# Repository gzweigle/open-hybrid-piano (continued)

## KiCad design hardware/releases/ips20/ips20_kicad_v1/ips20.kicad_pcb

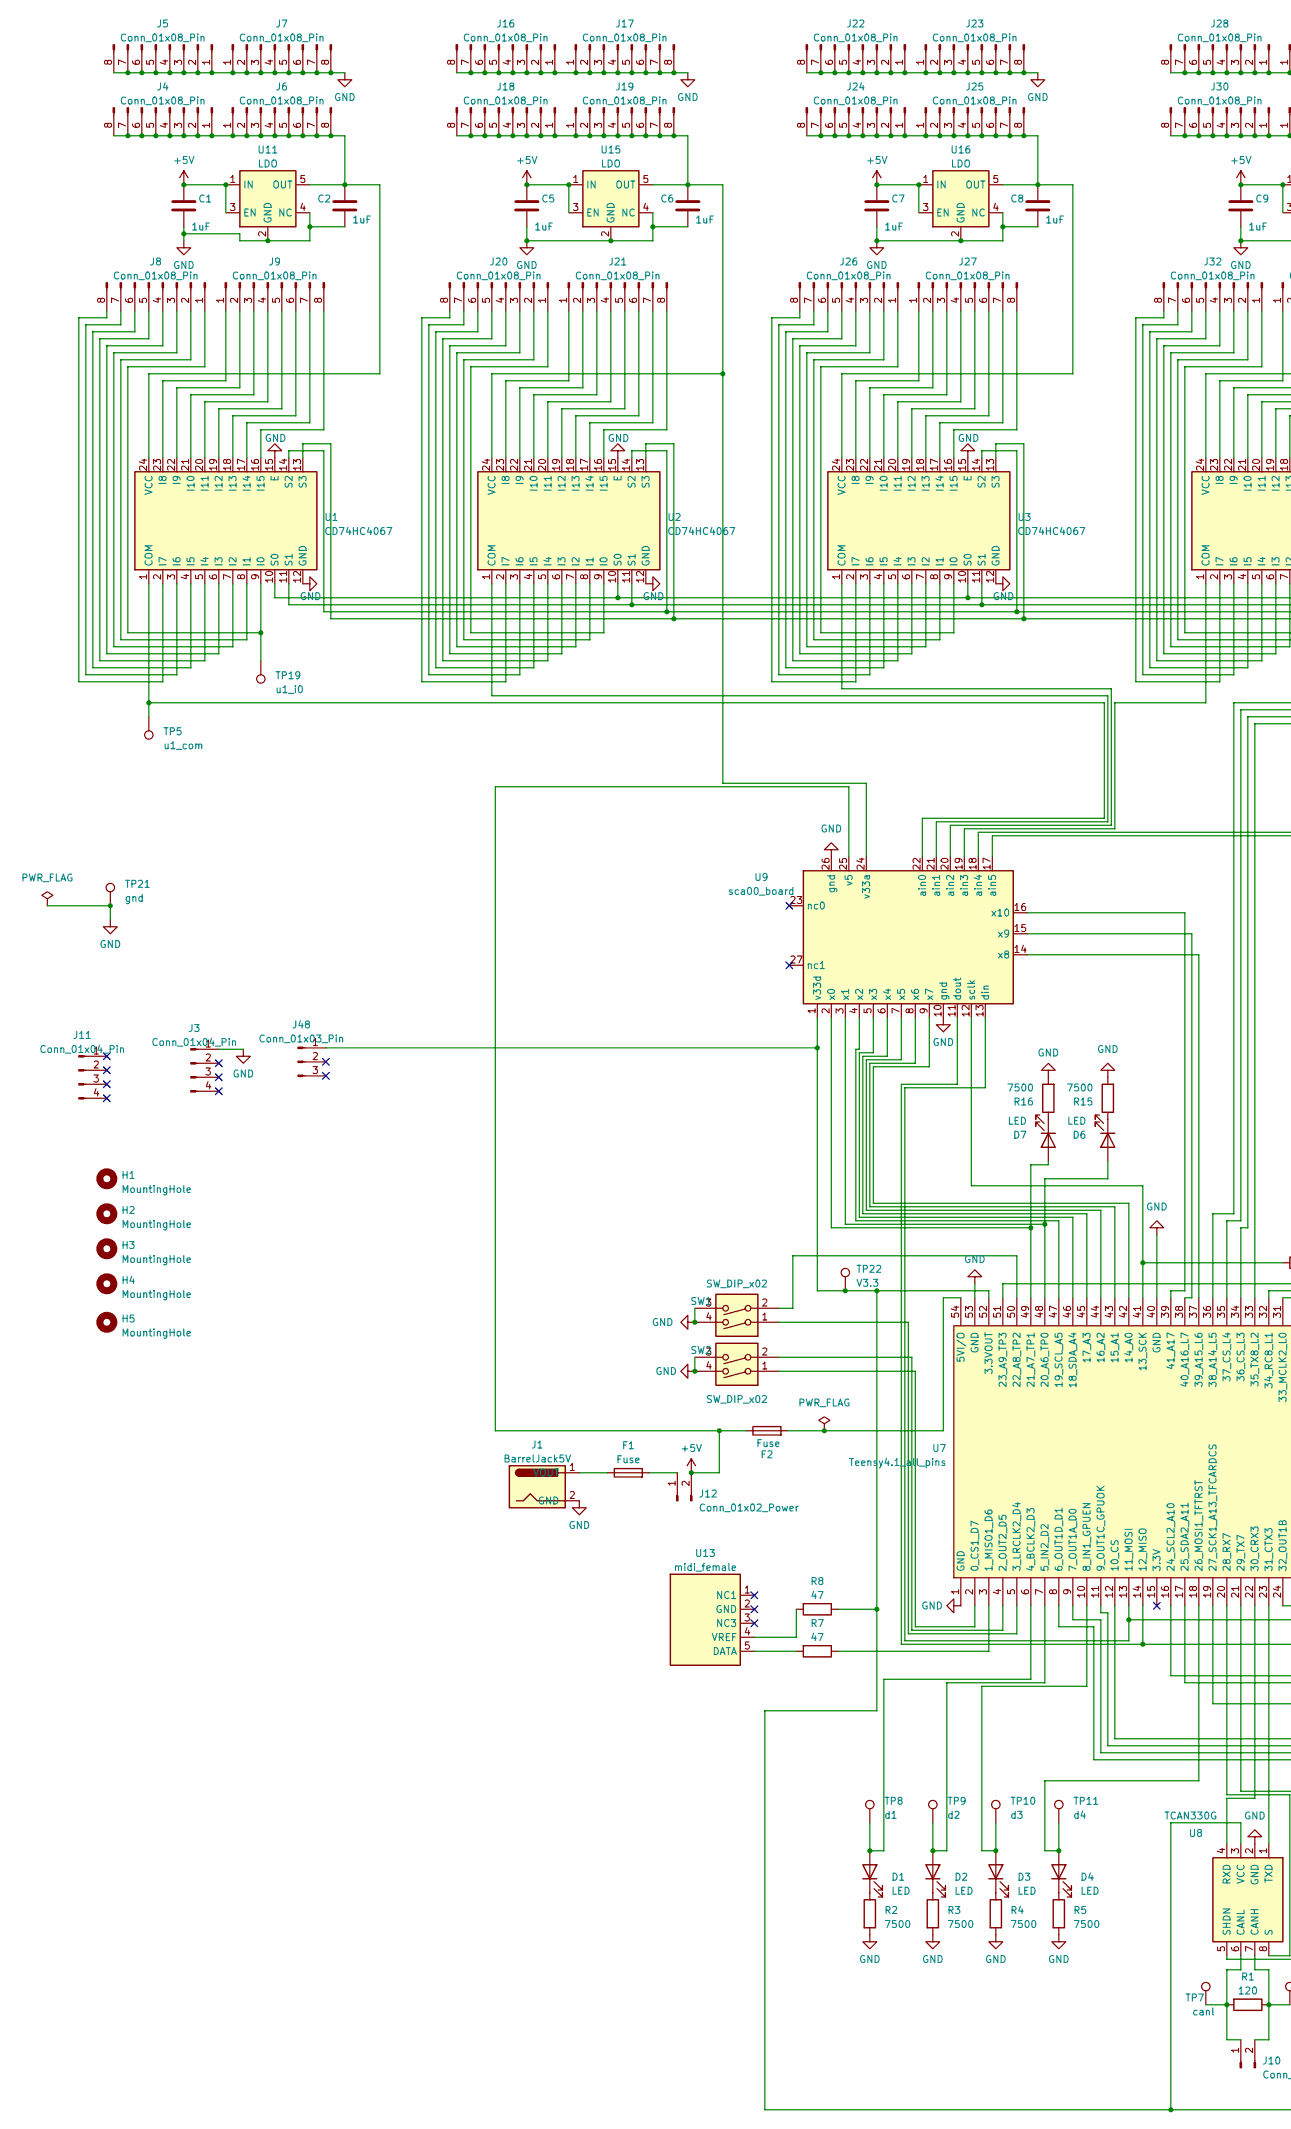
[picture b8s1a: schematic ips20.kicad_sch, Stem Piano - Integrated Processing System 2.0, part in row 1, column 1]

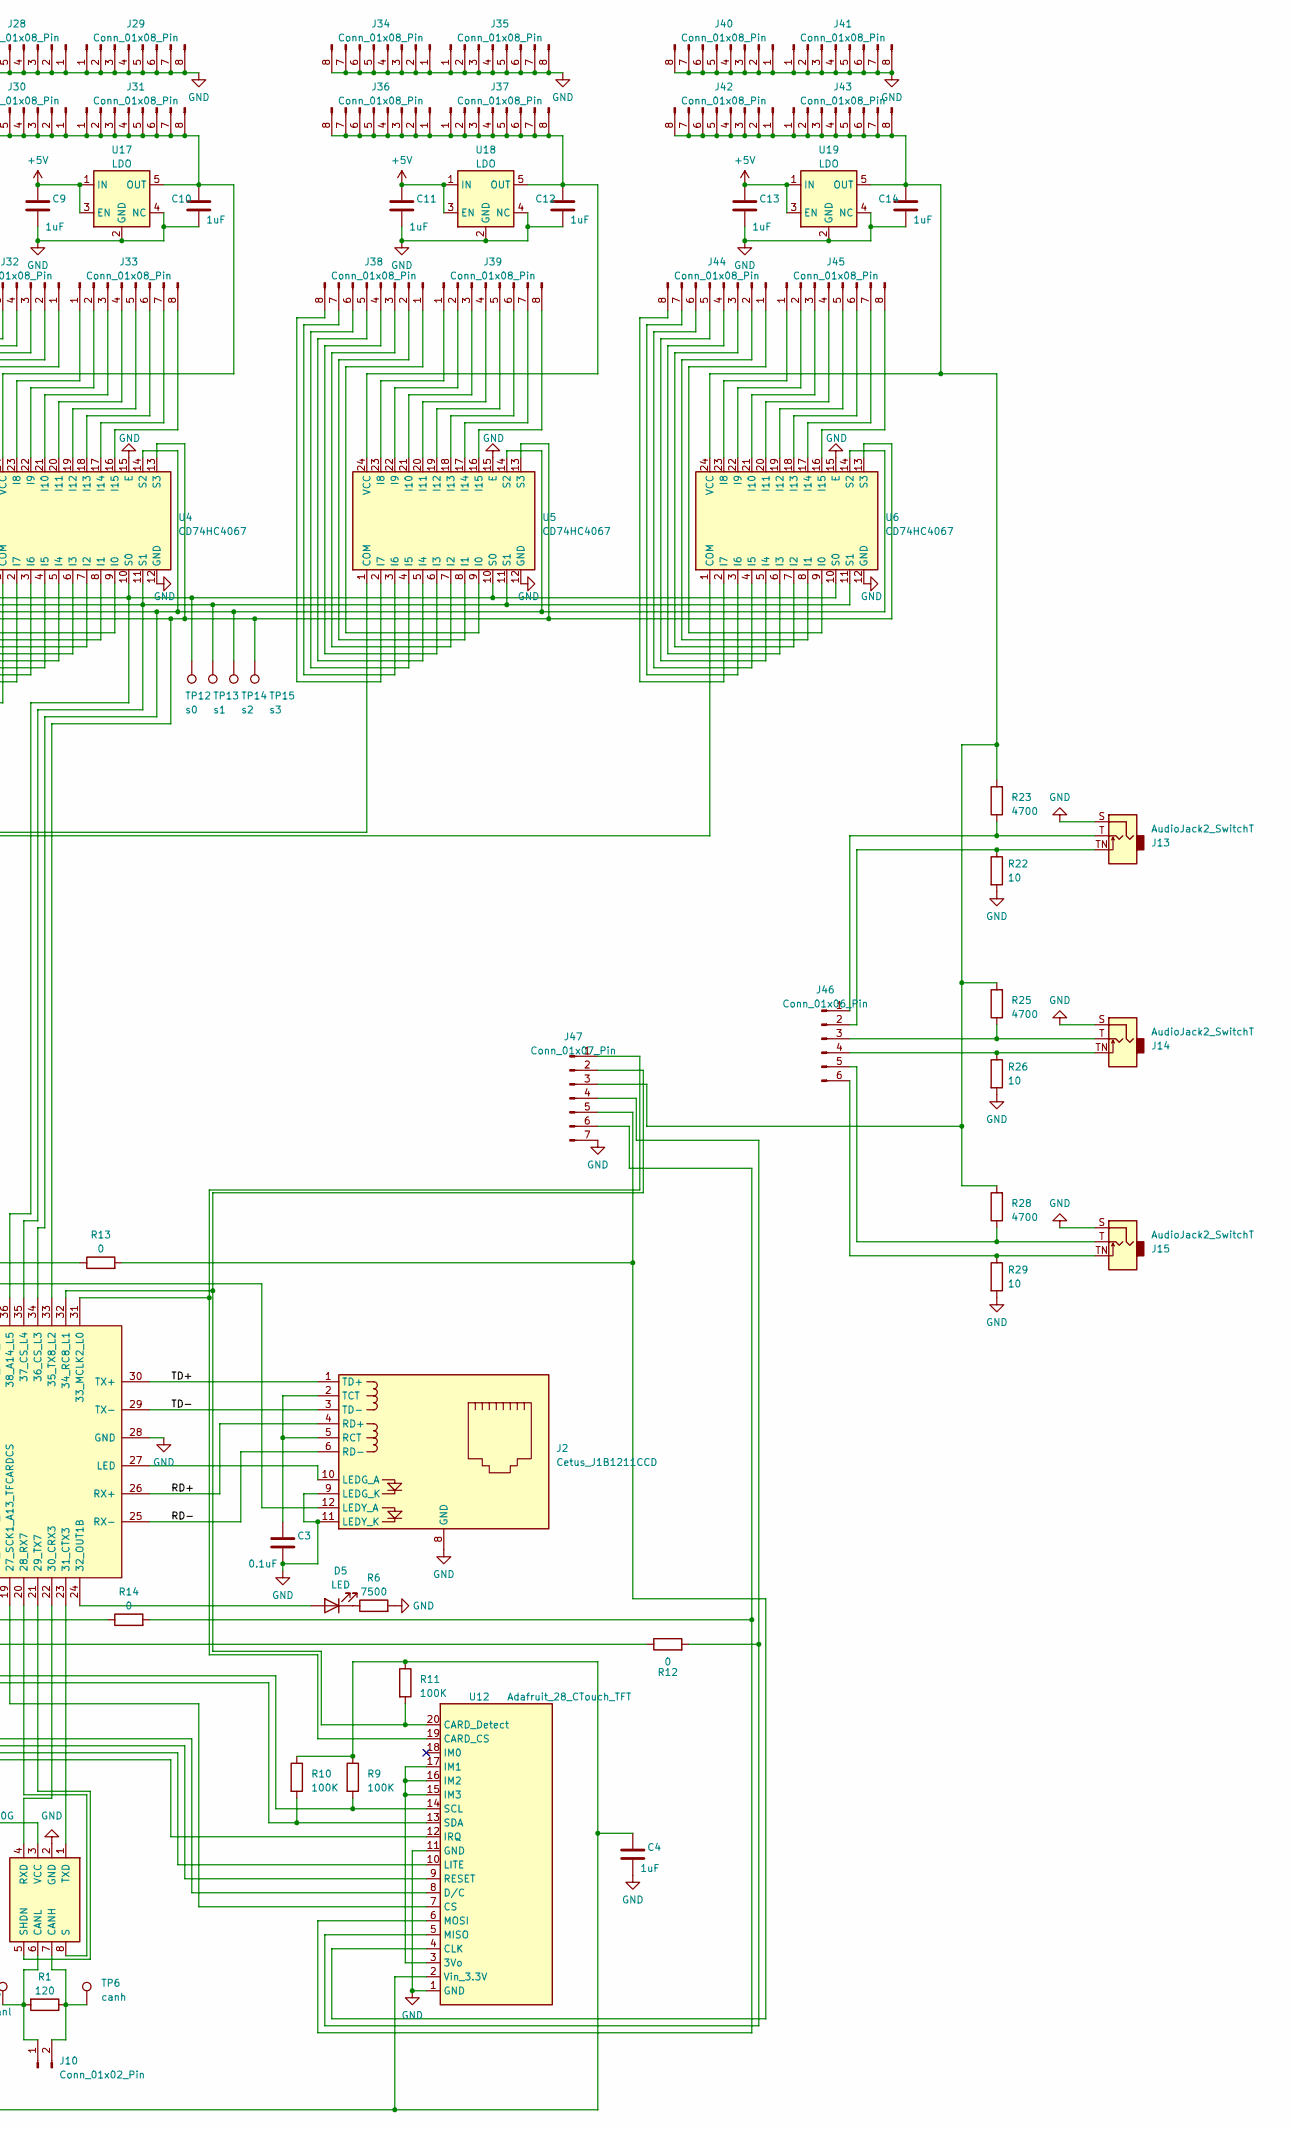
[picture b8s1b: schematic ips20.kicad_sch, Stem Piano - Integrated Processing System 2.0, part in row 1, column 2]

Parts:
C1, C2, C4, C5, C6, C7, C8, C9, C10, C11, C12, C13, C14: 1uF; C_0805_2012_1.18x1.45mm_medpad
C3: 0.1uF; C_0805_2012_1.18x1.45mm_medpad
D1, D2, D3, D4, D5, D6, D7: LED; LED_0805_2012_1.18x1.45mm_medpad2
F1, F2: Fuse; fp1210_3225_1.30x2.65mm_medpad
H1, H2, H3, H4, H5: MountingHole; MountingHole_2.2mm_M2_DIN965_Pad_TopBottom
J1: BarrelJack5V; BarrelJack_Horizontal_correct_edge
J2: Cetus_J1B1211CCD; RJ45_Cetus_J1B1211CCD_correct_edge
J3, J11: Conn_01x04_Pin; PinHeader_1x04_P2.54mm_Vertical
J4, J5, J6, J7, J8, J9, J16, J17, J18, J19, J20, J21, J22, J23, J24, J25, J26, J27, J28, J29, J30, J31, J32, J33, J34, J35, J36, J37, J38, J39, J40, J41, J42, J43, J44, J45: Conn_01x08_Pin; PinHeader_1x08_P2.54mm_Vertical_smallcourtyard
J10: Conn_01x02_Pin; PinHeader_1x02_P2.54mm_Vertical
J12: Conn_01x02_Power; PinHeader_1x02_P2.54mm_Vertical
J13, J14, J15: AudioJack2_SwitchT; uxcell_audio_quarter_inch
J46: Conn_01x06_Pin; PinHeader_1x06_P2.54mm_Vertical
J47: Conn_01x07_Pin; PinSocket_1x07_P2.54mm_Vertical
J48: Conn_01x03_Pin; PinSocket_1x03_P2.54mm_Vertical
R1: 120; R_0805_2012_1.20x1.40mm_medpad
R2, R3, R4, R5, R6, R15, R16: 7500; R_0805_2012_1.20x1.40mm_medpad
R7, R8: 47; R_0805_2012_1.20x1.40mm_medpad
R9, R10, R11: 100K; R_0805_2012_1.20x1.40mm_medpad
R12, R13, R14: 0; R_0805_2012_1.20x1.40mm_medpad
R22, R26, R29: 10; R_0805_2012_1.20x1.40mm_medpad
R23, R25, R28: 4700; R_0805_2012_1.20x1.40mm_medpad
SW1, SW2: SW_DIP_x02; SW_DIP_SPSTx02_Slide_medpad
TP5: u1_com; TestPoint_Keystone_5000-5004_Miniature
TP6: canh; TestPoint_Keystone_5000-5004_Miniature
TP7: canl; TestPoint_Keystone_5000-5004_Miniature
TP8: d1; TestPoint_Keystone_5000-5004_Miniature
TP9: d2; TestPoint_Keystone_5000-5004_Miniature
TP10: d3; TestPoint_Keystone_5000-5004_Miniature
TP11: d4; TestPoint_Keystone_5000-5004_Miniature
TP12: s0; TestPoint_Keystone_5000-5004_Miniature
TP13: s1; TestPoint_Keystone_5000-5004_Miniature
TP14: s2; TestPoint_Keystone_5000-5004_Miniature
TP15: s3; TestPoint_Keystone_5000-5004_Miniature
TP19: u1_i0; TestPoint_Keystone_5000-5004_Miniature
TP21: gnd; TestPoint_Keystone_5000-5004_Miniature
TP22: V3.3; TestPoint_Keystone_5000-5004_Miniature
U1, U2, U3, U4, U5, U6: CD74HC4067; SOIC-24_7.5x15.4mm_P1.27mm_medpad
U7: Teensy4.1_all_pins; Teensy41_ringpads
U8: TCAN330G; SOIC-8_3.9x4.9mm_P1.27mm_medpad
U9: sca00_board
U11, U15, U16, U17, U18, U19: LDO; SOT-23-5_medpad
U12: Adafruit_28_CTouch_TFT; PinHeader_1x20_P2.54mm_Vertical
U13: midi_female; midi_rightangle_female

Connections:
+5V: C1.1, C5.1, C7.1, C9.1, C11.1, C13.1, F2.1, J12.2, U9.25 (v5), U11.1 (IN), U11.3 (EN), U15.1 (IN), U15.3 (EN), U16.1 (IN), U16.3 (EN), U17.1 (IN), U17.3 (EN), U18.1 (IN), U18.3 (EN), U19.1 (IN), U19.3 (EN)
/RD+: J2.4 (RD+), U7.26 (RX+)
/RD-: J2.6 (RD-), U7.25 (RX-)
/TD+: J2.1 (TD+), U7.30 (TX+)
/TD-: J2.3 (TD-), U7.29 (TX-)
GND: C1.2, C2.2, C3.2, C4.2, C5.2, C6.2, C7.2, C8.2, C9.2, C10.2, C11.2, C12.2, C13.2, C14.2, J1.2 (GND), J2.8 (GND), J2.9 (LEDG_K), J2.11 (LEDY_K), J3.1, J5.1, J5.2, J5.3, J5.4, J5.5, J5.6, J5.7, J5.8, J7.1, J7.2, J7.3, J7.4, J7.5, J7.6, J7.7, J7.8, J13.S, J14.S, J15.S, J16.1, J16.2, J16.3, J16.4, J16.5, J16.6, J16.7, J16.8, J17.1, J17.2, J17.3, J17.4, J17.5, J17.6, J17.7, J17.8, J22.1, J22.2, J22.3, J22.4, J22.5, J22.6, J22.7, J22.8, J23.1, J23.2, J23.3, J23.4, J23.5, J23.6, J23.7, J23.8, J28.1, J28.2, J28.3, J28.4, J28.5, J28.6, J28.7, J28.8, J29.1, J29.2, J29.3, J29.4, J29.5, J29.6, J29.7, J29.8, J34.1, J34.2, J34.3, J34.4, J34.5, J34.6, J34.7, J34.8, J35.1, J35.2, J35.3, J35.4, J35.5, J35.6, J35.7, J35.8, J40.1, J40.2, J40.3, J40.4, J40.5, J40.6, J40.7, J40.8, J41.1, J41.2, J41.3, J41.4, J41.5, J41.6, J41.7, J41.8, J47.7, R2.2, R3.2, R4.2, R5.2, R6.2, R15.2, R16.2, R22.2, R26.2, R29.2, SW1.3, SW1.4, SW2.3, SW2.4, TP21.1, U1.12 (GND), U1.15 (E), U2.12 (GND), U2.15 (E), U3.12 (GND), U3.15 (E), U4.12 (GND), U4.15 (E), U5.12 (GND), U5.15 (E), U6.12 (GND), U6.15 (E), U7.1 (GND), U7.28 (GND), U7.40 (GND), U7.53 (GND), U8.2 (GND), U9.10 (gnd), U9.26 (gnd), U11.2 (GND), U11.4 (NC), U12.1 (GND), U12.11 (GND), U15.2 (GND), U15.4 (NC), U16.2 (GND), U16.4 (NC), U17.2 (GND), U17.4 (NC), U18.2 (GND), U18.4 (NC), U19.2 (GND), U19.4 (NC)
unnamed: D1.2 (A), TP8.1, U7.6 (4_BCLK2_D3)
unnamed: D1.1 (K), R2.1
unnamed: D2.2 (A), TP9.1, U7.7 (5_IN2_D2)
unnamed: D2.1 (K), R3.1
unnamed: D3.2 (A), TP10.1, U7.10 (8_IN1_GPUEN)
unnamed: D3.1 (K), R4.1
unnamed: D4.2 (A), TP11.1, U7.18 (26_MOSI1_TFTRST)
unnamed: D4.1 (K), R5.1
unnamed: D5.2 (A), U7.24 (32_OUT1B)
unnamed: D5.1 (K), R6.1
unnamed: D6.2 (A), U7.48 (20_A6_TP0), U9.3 (x1)
unnamed: D6.1 (K), R15.1
unnamed: D7.2 (A), U7.49 (21_A7_TP1), U9.2 (x0)
unnamed: D7.1 (K), R16.1
unnamed: F1.1, J1.1 (VOUT)
unnamed: J2.10 (LEDG_A), U7.27 (LED)
unnamed: J2.12 (LEDY_A), U7.51 (23_A9_TP3)
unnamed: C3.1, J2.2 (TCT), J2.5 (RCT)
unnamed: C2.1, J4.1, J4.2, J4.3, J4.4, J4.5, J4.6, J4.7, J4.8, J6.1, J6.2, J6.3, J6.4, J6.5, J6.6, J6.7, J6.8, U1.24 (VCC), U11.5 (OUT)
unnamed: J8.1, TP19.1, U1.9 (I0)
unnamed: J8.2, U1.8 (I1)
unnamed: J8.3, U1.7 (I2)
unnamed: J8.4, U1.6 (I3)
unnamed: J8.5, U1.5 (I4)
unnamed: J8.6, U1.4 (I5)
unnamed: J8.7, U1.3 (I6)
unnamed: J8.8, U1.2 (I7)
unnamed: J9.1, U1.23 (I8)
unnamed: J9.2, U1.22 (I9)
unnamed: J9.3, U1.21 (I10)
unnamed: J9.4, U1.20 (I11)
unnamed: J9.5, U1.19 (I12)
unnamed: J9.6, U1.18 (I13)
unnamed: J9.7, U1.17 (I14)
unnamed: J9.8, U1.16 (I15)
unnamed: J10.1, R1.2, TP7.1, U8.6 (CANL)
unnamed: J10.2, R1.1, TP6.1, U8.7 (CANH)
unnamed: F1.2, J12.1
unnamed: C6.1, J18.1, J18.2, J18.3, J18.4, J18.5, J18.6, J18.7, J18.8, J19.1, J19.2, J19.3, J19.4, J19.5, J19.6, J19.7, J19.8, U2.24 (VCC), U9.24 (v33a), U15.5 (OUT)
unnamed: J20.1, U2.9 (I0)
unnamed: J20.2, U2.8 (I1)
unnamed: J20.3, U2.7 (I2)
unnamed: J20.4, U2.6 (I3)
unnamed: J20.5, U2.5 (I4)
unnamed: J20.6, U2.4 (I5)
unnamed: J20.7, U2.3 (I6)
unnamed: J20.8, U2.2 (I7)
unnamed: J21.1, U2.23 (I8)
unnamed: J21.2, U2.22 (I9)
unnamed: J21.3, U2.21 (I10)
unnamed: J21.4, U2.20 (I11)
unnamed: J21.5, U2.19 (I12)
unnamed: J21.6, U2.18 (I13)
unnamed: J21.7, U2.17 (I14)
unnamed: J21.8, U2.16 (I15)
unnamed: C8.1, J24.1, J24.2, J24.3, J24.4, J24.5, J24.6, J24.7, J24.8, J25.1, J25.2, J25.3, J25.4, J25.5, J25.6, J25.7, J25.8, U3.24 (VCC), U16.5 (OUT)
unnamed: J26.1, U3.9 (I0)
unnamed: J26.2, U3.8 (I1)
unnamed: J26.3, U3.7 (I2)
unnamed: J26.4, U3.6 (I3)
unnamed: J26.5, U3.5 (I4)
unnamed: J26.6, U3.4 (I5)
unnamed: J26.7, U3.3 (I6)
unnamed: J26.8, U3.2 (I7)
unnamed: J27.1, U3.23 (I8)
unnamed: J27.2, U3.22 (I9)
unnamed: J27.3, U3.21 (I10)
unnamed: J27.4, U3.20 (I11)
unnamed: J27.5, U3.19 (I12)
unnamed: J27.6, U3.18 (I13)
unnamed: J27.7, U3.17 (I14)
unnamed: J27.8, U3.16 (I15)
unnamed: C10.1, J30.1, J30.2, J30.3, J30.4, J30.5, J30.6, J30.7, J30.8, J31.1, J31.2, J31.3, J31.4, J31.5, J31.6, J31.7, J31.8, U4.24 (VCC), U17.5 (OUT)
unnamed: J32.1, U4.9 (I0)
unnamed: J32.2, U4.8 (I1)
unnamed: J32.3, U4.7 (I2)
unnamed: J32.4, U4.6 (I3)
unnamed: J32.5, U4.5 (I4)
unnamed: J32.6, U4.4 (I5)
unnamed: J32.7, U4.3 (I6)
unnamed: J32.8, U4.2 (I7)
unnamed: J33.1, U4.23 (I8)
unnamed: J33.2, U4.22 (I9)
unnamed: J33.3, U4.21 (I10)
unnamed: J33.4, U4.20 (I11)
unnamed: J33.5, U4.19 (I12)
unnamed: J33.6, U4.18 (I13)
unnamed: J33.7, U4.17 (I14)
unnamed: J33.8, U4.16 (I15)
unnamed: C12.1, J36.1, J36.2, J36.3, J36.4, J36.5, J36.6, J36.7, J36.8, J37.1, J37.2, J37.3, J37.4, J37.5, J37.6, J37.7, J37.8, U5.24 (VCC), U18.5 (OUT)
unnamed: J38.1, U5.9 (I0)
unnamed: J38.2, U5.8 (I1)
unnamed: J38.3, U5.7 (I2)
unnamed: J38.4, U5.6 (I3)
unnamed: J38.5, U5.5 (I4)
unnamed: J38.6, U5.4 (I5)
unnamed: J38.7, U5.3 (I6)
unnamed: J38.8, U5.2 (I7)
unnamed: J39.1, U5.23 (I8)
unnamed: J39.2, U5.22 (I9)
unnamed: J39.3, U5.21 (I10)
unnamed: J39.4, U5.20 (I11)
unnamed: J39.5, U5.19 (I12)
unnamed: J39.6, U5.18 (I13)
unnamed: J39.7, U5.17 (I14)
unnamed: J39.8, U5.16 (I15)
unnamed: C14.1, J42.1, J42.2, J42.3, J42.4, J42.5, J42.6, J42.7, J42.8, J43.1, J43.2, J43.3, J43.4, J43.5, J43.6, J43.7, J43.8, J47.3, R23.2, R25.2, R28.2, U6.24 (VCC), U19.5 (OUT)
unnamed: J44.1, U6.9 (I0)
unnamed: J44.2, U6.8 (I1)
unnamed: J44.3, U6.7 (I2)
unnamed: J44.4, U6.6 (I3)
unnamed: J44.5, U6.5 (I4)
unnamed: J44.6, U6.4 (I5)
unnamed: J44.7, U6.3 (I6)
unnamed: J44.8, U6.2 (I7)
unnamed: J45.1, U6.23 (I8)
unnamed: J45.2, U6.22 (I9)
unnamed: J45.3, U6.21 (I10)
unnamed: J45.4, U6.20 (I11)
unnamed: J45.5, U6.19 (I12)
unnamed: J45.6, U6.18 (I13)
unnamed: J45.7, U6.17 (I14)
unnamed: J45.8, U6.16 (I15)
unnamed: J13.T, J46.1, R23.1
unnamed: J13.TN, J46.2, R22.1
unnamed: J14.T, J46.3, R25.1
unnamed: J14.TN, J46.4, R26.1
unnamed: J15.T, J46.5, R28.1
unnamed: J15.TN, J46.6, R29.1
unnamed: J47.1, U7.31 (33_MCLK2_L0), U12.19 (CARD_CS)
unnamed: J47.2, R11.2, U7.32 (34_RC8_L1), U12.20 (CARD_Detect)
unnamed: J47.4, R12.2, U12.5 (MISO)
unnamed: J47.5, R13.2, U12.4 (CLK)
unnamed: J47.6, R14.2, U12.6 (MOSI)
unnamed: C4.1, J48.1, R8.1, R9.1, R10.1, R11.1, TP22.1, U7.52 (3.3VOUT), U8.3 (VCC), U9.1 (v33d), U12.2 (Vin_3.3V)
unnamed: TP5.1, U1.1 (COM), U9.22 (ain0)
unnamed: TP12.1, U1.10 (S0), U2.10 (S0), U3.10 (S0), U4.10 (S0), U5.10 (S0), U6.10 (S0), U7.36 (38_A14_L5)
unnamed: TP13.1, U1.11 (S1), U2.11 (S1), U3.11 (S1), U4.11 (S1), U5.11 (S1), U6.11 (S1), U7.35 (37_CS_L4)
unnamed: TP14.1, U1.14 (S2), U2.14 (S2), U3.14 (S2), U4.14 (S2), U5.14 (S2), U6.14 (S2), U7.34 (36_CS_L3)
unnamed: TP15.1, U1.13 (S3), U2.13 (S3), U3.13 (S3), U4.13 (S3), U5.13 (S3), U6.13 (S3), U7.33 (35_TX8_L2)
unnamed: U2.1 (COM), U9.21 (ain1)
unnamed: U3.1 (COM), U9.20 (ain2)
unnamed: U4.1 (COM), U9.19 (ain3)
unnamed: U5.1 (COM), U9.18 (ain4)
unnamed: U6.1 (COM), U9.17 (ain5)
unnamed: SW2.1, U7.2 (0_CS1_D7)
unnamed: R7.1, U7.3 (1_MISO1_D6)
unnamed: SW2.2, U7.4 (2_OUT2_D5)
unnamed: SW1.1, U7.5 (3_LRCLK2_D4)
unnamed: F2.2, U7.54 (5VI/O)
unnamed: R14.1, U7.13 (11_MOSI), U9.13 (din)
unnamed: R12.1, U7.14 (12_MISO), U9.11 (dout)
unnamed: R13.1, U7.41 (13_SCK), U9.12 (sclk)
unnamed: U7.42 (14_A0), U9.9 (x7)
unnamed: U7.43 (15_A1), U9.8 (x6)
unnamed: U7.44 (16_A2), U9.7 (x5)
unnamed: U7.45 (17_A3), U9.6 (x4)
unnamed: U7.46 (18_SDA_A4), U9.5 (x3)
unnamed: U7.47 (19_SCL_A5), U9.4 (x2)
unnamed: SW1.2, U7.50 (22_A8_TP2)
unnamed: U7.20 (28_RX7), U8.8 (S)
unnamed: U7.21 (29_TX7), U8.5 (SHDN)
unnamed: U7.22 (30_CRX3), U8.4 (RXD)
unnamed: U7.23 (31_CTX3), U8.1 (TXD)
unnamed: U7.37 (39_A15_L6), U9.14 (x8)
unnamed: U7.38 (40_A16_L7), U9.15 (x9)
unnamed: U7.39 (41_A17), U9.16 (x10)
unnamed: U12.3 (3Vo), U12.15 (IM3), U12.16 (IM2), U12.17 (IM1)
unnamed: U7.19 (27_SCK1_A13_TFCARDCS), U12.7 (CS)
unnamed: U7.12 (10_CS), U12.8 (D/C)
unnamed: U7.8 (6_OUT1D_D1), U12.12 (IRQ)
unnamed: U7.9 (7_OUT1A_D0), U12.10 (LITE)
unnamed: U7.11 (9_OUT1C_GPUOK), U12.9 (RESET)
unnamed: R9.2, U7.16 (24_SCL2_A10), U12.14 (SCL)
unnamed: R10.2, U7.17 (25_SDA2_A11), U12.13 (SDA)
unnamed: R7.2, U13.5 (DATA)
unnamed: R8.2, U13.4 (VREF)

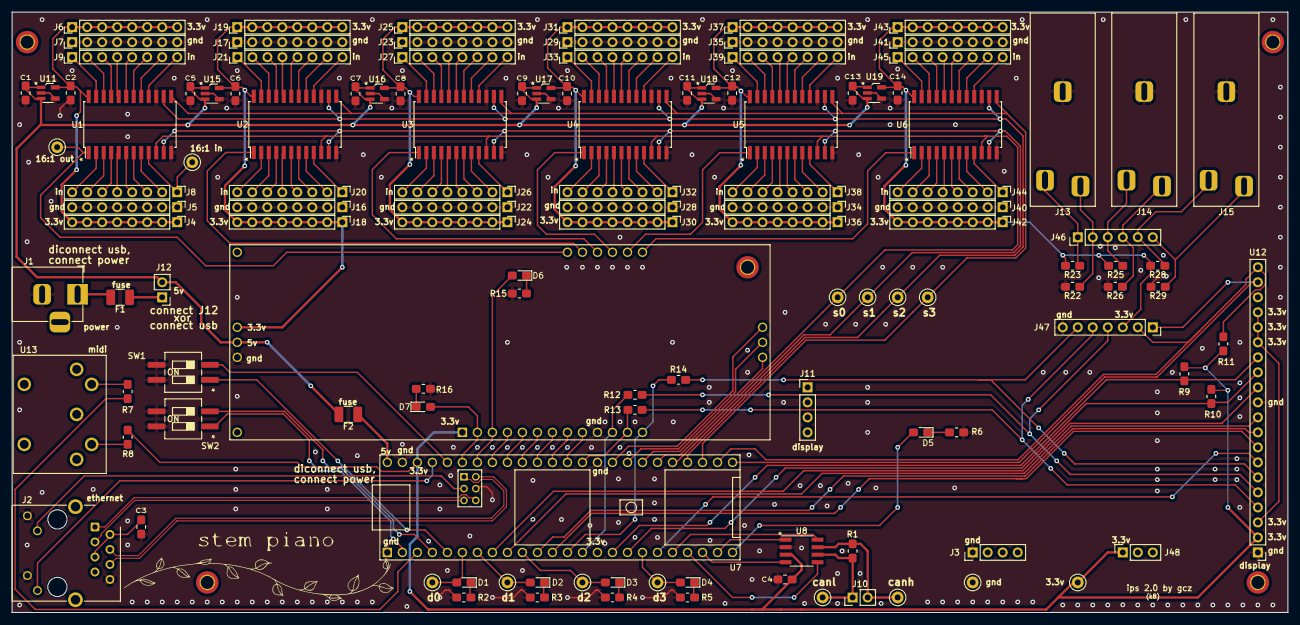
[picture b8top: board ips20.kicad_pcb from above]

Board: 2 copper layers, 215.9 x 101.6 mm, 131 parts (0 on the bottom side), 183 nets.

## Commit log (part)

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2022-01-02 Add block diagram
2022-01-10 test
2022-01-10 hammer samples and quick analysis
2022-01-10 clarify v location, add figures
2022-01-10 clarify velocity, add figures
2022-01-10 zoom in for velocity figure
2022-01-23 add hardware units
2022-01-23 step 14 code
2022-01-30 Completed step 14, add video link
2022-02-08 simple get ADC example
2022-10-24 update completed steps in README
2023-02-07 add steps 20, 21, 22
2023-02-07 split readme
2023-02-07 readme change
2023-02-07 videos
2023-03-13 format
2023-03-13 new single board option
2023-03-13 IPS spec
2023-03-13 video update
2023-03-13 added components
2023-03-13 list components
2023-03-13 title
2023-04-23 step 24
2023-06-09 reorg
2023-06-09 dpp board bringup code
2023-06-09 create license
2023-06-09 test single CNY70
2023-06-09 damper board
2023-06-09 step 25 video
2023-06-09 link for LTC
2023-06-10 diag and dip to dpp
2023-06-10 settings file
2023-06-10 placeholders
2023-07-29 bill of materials
2023-07-29 restore spec
2023-07-29 video #26
2023-07-29 update bill of materials
2023-07-29 release process
2023-07-30 packages process to build a complete piano
2023-08-07 organization
2023-08-07 ips2 hammer damper top code
2023-08-08 ips2 include
2023-08-08 ips2 midi
2023-08-08 add open source license for the hardware
2023-08-08 open source license for the hardware
2023-08-08 update midi
2023-08-09 hammer position sensor 0.6 pcb
2023-08-09 hammer position sensor pcb 0.6
2023-08-09 hammer position sensor pcb 0.4
2023-08-11 stem piano g
2023-08-12 contributing guidelines
2023-08-12 more contributing guidelines
2023-08-12 under construction
2023-08-17 power supplies
2023-08-17 power supply
2023-08-17 fuse
2023-08-17 supply warning
2023-08-17 fuse wording
2023-08-21 pedal processing
2023-08-23 tft display
2023-08-27 license, documentation
2023-08-28 improve
2023-11-12 hammer and damper working
2023-11-17 hammer and damper subset 0
2023-11-26 sca00 PCB plus FW releases
2023-11-26 sca00 PCB
2023-11-26 sca00 PCB (2)
2023-11-26 StemPianoIPS2 misc updates
2023-11-26 sca00 schematic
2023-11-26 board2board.cpp
2023-11-26 library misc
2023-11-26 ADC driver
2023-11-26 damper processing
2023-11-26 hammer algorithm
2023-11-26 SCA 2.0 PCB
2023-11-26 IPS 2.0 PCB
2023-11-26 Stem Piano G doc
2023-11-26 show and tell
2023-11-26 video
2023-12-10 doc- clarify SCA board count
2023-12-12 doc updates
2023-12-15 hps hardware details
2023-12-17 cost estimates
2023-12-18 damper_settings.cpp - pedals
2023-12-18 readme update
2023-12-18 contributing
2023-12-19 packages -> pianos
2023-12-19 security policy
2023-12-19 update contrib
2023-12-27 costs
2023-12-27 screen
2023-12-27 name
2023-12-28 overview
2024-01-04 dynamic range R and Vref
2024-01-06 more help
2024-01-06 faster damper sampling
2024-01-06 hammer settings
2024-01-06 eliminate need for extra settling
2024-01-06 address comment
2024-01-06 faster sampling
2024-01-06 conversion nanoseconds
2024-01-06 faster pipeline
2024-01-07 update R2
2024-01-07 R2 selection advice
2024-01-07 hps07 g
2024-01-07 hps04 R2
2024-01-14 add design dir
2024-01-14 HPS characterize
2024-01-15 data readme
2024-01-15 hps characterize readme
2024-01-15 Ethernet receive
2024-01-15 response analysis
2024-01-15 hammer crane
2024-01-15 hybrid ref
2024-01-24 project is not done
2024-02-22 comment on volume consistency
2024-03-16 video on mechanical
2024-03-17 documentation
2024-03-17 misc updates after new video
2024-03-31 date
2024-03-31 18b and ref
2024-03-31 action information
2024-03-31 network as using
2024-03-31 add utilities class
2024-03-31 simplify gain control
2024-03-31 eliminate adaptive threshold
2024-03-31 simplify thresholds
2024-03-31 update status
2024-03-31 util,cal,simpler datapath, debug
2024-03-31 more analog options, ethernet update
2024-03-31 adjust settings based on playing
2024-03-31 build instructions
2024-04-03 fix HPS R2 value
2024-04-03 not not done
2024-04-06 audio system warning
2024-04-06 detailed build instructions - more
2024-04-06 more build instructions
2024-04-07 fasteners and measured distances
2024-04-07 spec hammer and sensor bars
2024-04-07 review
2024-04-07 add KiCad projects
2024-04-07 hw readme
2024-04-08 kicad info link
2024-04-08 clarify
2024-04-13 misc updates, light source
2024-04-14 data acq timing diagrams
2024-04-20 add auto mute functionality
2024-04-20 further auto mute
2024-04-20 calibration - partial
2024-04-20 more autocal
2024-04-21 refactor status and led
2024-04-22 note parts back of PCB
2024-04-22 better serial monitor output and debug
2024-04-22 update warning doc
2024-04-27 link new stem-piano location
2024-04-27 hps 0.8 initial
2024-04-28 issue 39 - IF
2024-04-28 adjust HPS R values
2024-04-29 HPS 0.8 update
2024-04-29 HPS 0.8 further clarify
2024-05-04 new config switch func
2024-05-04 new config settings
2024-05-04 velocity calibration
2024-05-05 fix extra serial info
2024-05-05 15-14ms and hps08 gerber
2024-05-11 store cal in eeprom
2024-05-11 eeprom info to warnings
2024-05-11 optional RV
2024-05-12 test cool tft idea
2024-05-12 better fuse approach
2024-06-08 add PLS circuit board
2024-06-09 issue 32
2024-06-09 new video, explain repos
2024-06-09 fix issue 51 - setup network
2024-06-09 issue 29 - midi buffer
2024-06-09 hps08 and pls00 kicad
2024-06-10 issue 48 - indicate eeprom write
2024-06-15 issue 45 - LDO current
2024-06-15 issue 54 - TN pulldown
2024-06-15 issue 41 - sca connection labels
2024-06-16 resistor values and hps info
2024-06-20 issue 53 - interposer board
2024-06-23 issue 62 - pedal resistors
2024-06-29 issues 61(speedup) and 59(high speed test mode)
2024-06-29 issue 60 - clipping
2024-06-29 issue 42 - max midi
2024-06-30 issue 46 - velocity scaling
2024-07-01 issue 65 - adj damper thresh
2024-07-01 issue 68 - ACE KiCad
2024-07-01 issue 66 - part inconsistency
2024-07-04 moving connectors for IPS on the bottom of the ACE board, per issue #70
2024-07-04 moving connectors for IPS on the bottom of the SCA board, per issue #70
2024-07-05 issue 69 (KiCad 8), 70 (label wrong side)
2024-07-12 help and warnings link
2024-07-14 clarify fuse
2024-07-14 correct sentence
2024-07-15 issue 78 - cut 5V pad
2024-07-21 issue 80 - cal double prec
2024-07-21 issue 31 - update damper code
2024-07-21 issue 74 - pedal component
2024-07-26 ips power doc update
2024-07-26 ips power doc
2024-07-27 issue 77 - add F2
2024-07-27 surface mount replace video link
2024-07-27 parts list reference
2024-07-27 sensor info
2024-07-28 describe part no
2024-08-10 issue 55 - velocity algorithm
2024-08-10 issue 84 - init nonv memory
2024-08-10 issue 81 - store cal as doubles
2024-08-10 default to no threshold algorithm
2024-09-02 issues 85 (adc scaling) and 86 (filter length)
2024-09-05 issue 88 - power jumper
2024-09-09 issue 92 - tft compile error
2024-09-15 fixes issue#93
2024-09-21 add #define for usb midi
2024-09-28 issue 97, 91, add new videos
2024-09-28 Issue 103 - fix comment
2024-09-28 issue - 104
2024-09-29 issue - 100 - custom wiring in FW
2024-10-02 experimental ACE with ethernet, aka 8P8C connectors
2024-10-02 footprint and symbol for the stacked 8P8C
2024-10-15 issue 108 - Ethernet values
2024-12-15 second piano milestone
2025-01-07 issue 101 - damper board compile
2025-04-23 issue 113 - add tcp streaming
2025-04-24 two not three bytes for single value Ethernet
2025-04-26 issue 114 - tcp long delay
2025-04-26 issue 115 - improve debug messages
2025-04-26 issue 118 - add display processor burden
2025-04-26 issue 115 (debug) and 117 (link)
2025-04-26 issue 119 - add tcp rcv software
2025-04-26 issue 101 - damper board compiling
2025-05-04 update videos with instructions links
2025-05-05 issue 116 - fix processor burden overrun on print
2025-05-05 issue 120 - speed up sample rate
2025-05-10 fix minor damper status interval bug
2025-05-12 issue 121 - damper board bug
2025-05-16 issue 122 - short sustain bug
2025-05-18 issue 96 - add ace labels
2025-05-18 issues 123, 125 - damper algorithm bugs
2025-05-18 issues 126, 127, 128
2025-05-31 issue 129 - add damper over Ethernet
2025-05-31 issue 130 - processor burden
2025-11-27 ignoring cache file
2025-11-29 Rename src_damper.ino to ips2_damper.ino
2025-11-29 Renamed to keep ArduinoIDE happy
2025-11-30 Symbolic links to ease ArduinoIDE compilation
